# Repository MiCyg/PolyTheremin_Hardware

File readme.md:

# Polytheremin Hardware

[← Back to main repository](https://github.com/MiCyg/PolyTheremin.git)

---

# PolyTheremin Test Platform  

# Description  

This test platform features a main board with four capacitive proximity sensors based on [OpenTheremin](https://github.com/GaudiLabs/OpenThereminV4) electronics.  

The key improvement in this version is the replacement of the fixed-frequency oscillator with a microcontroller-driven heterodyne frequency generator. This modification simplifies the circuit design and calibration process.  

The platform enables the analysis of antenna correlation errors, visualized on an XY plot.  
Its ultimate goal is to provide a functional example of a PolyTheremin with four independent oscillators, significantly reducing finger cross-correlation.

# PCB Characteristics  
- **Microcontroller**: RP2040  
- **LED**: One addressable LED for status indication  
- **Oscillator Modules**: Four theremin modules, independently connected to the microcontroller  
- **Audio Output**: Four 12-bit DACs (MCP4922) with a mixer and a 6.3mm jack socket  

# Block Schematic  

# 3D View  

# Contribution  

Contributions are welcome!  
If you have suggestions, encounter any issues, or want to discuss the project, feel free to contact me or open a pull request.

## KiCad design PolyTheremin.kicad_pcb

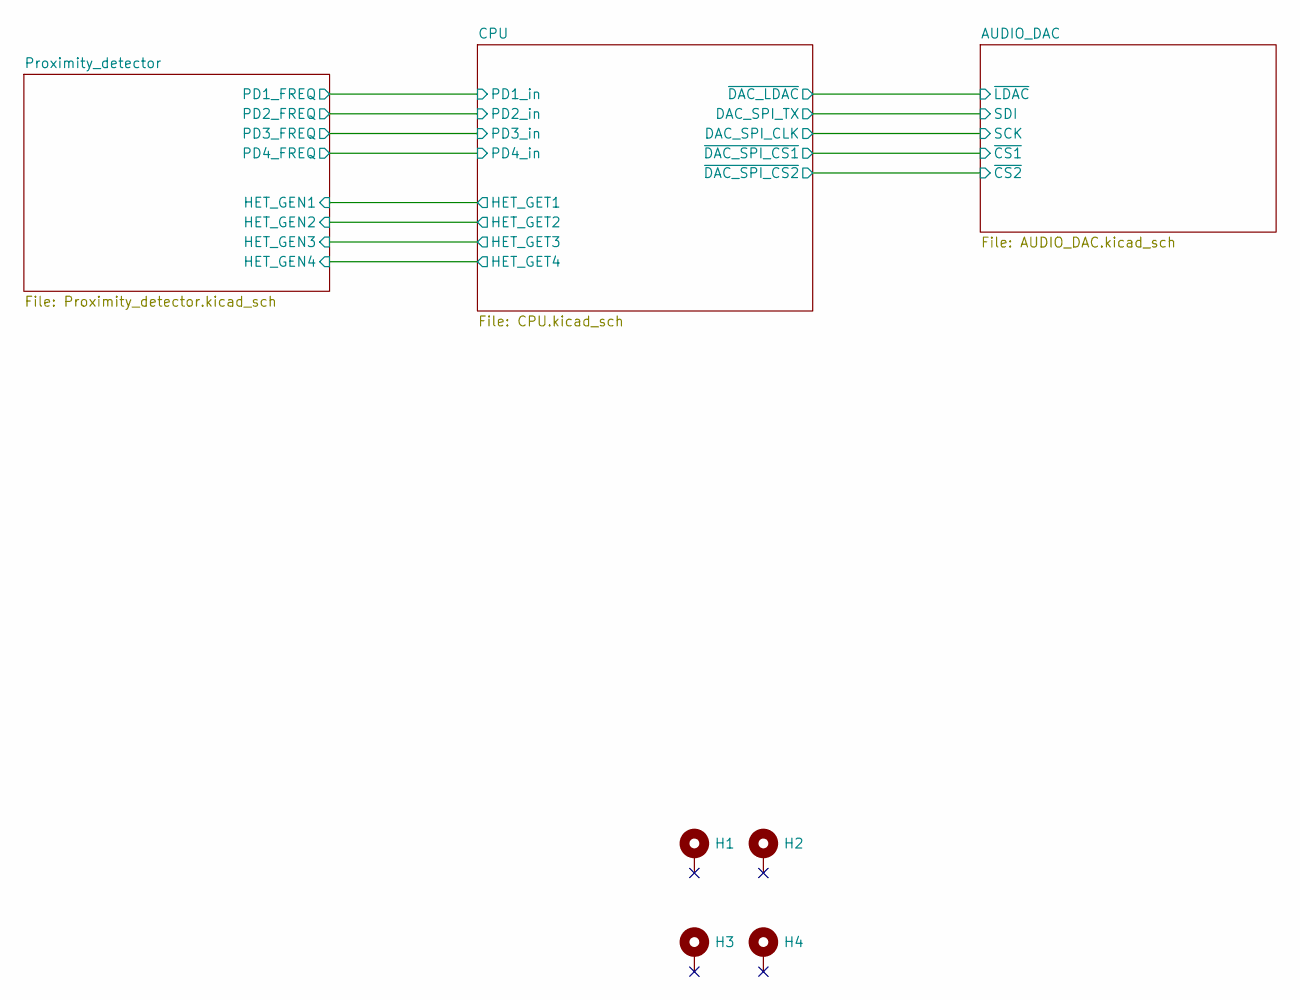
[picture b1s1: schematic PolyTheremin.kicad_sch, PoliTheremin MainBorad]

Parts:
H1, H2, H3, H4: MountingHole_Pad; MountingHole_3.2mm_M3_Pad_Via

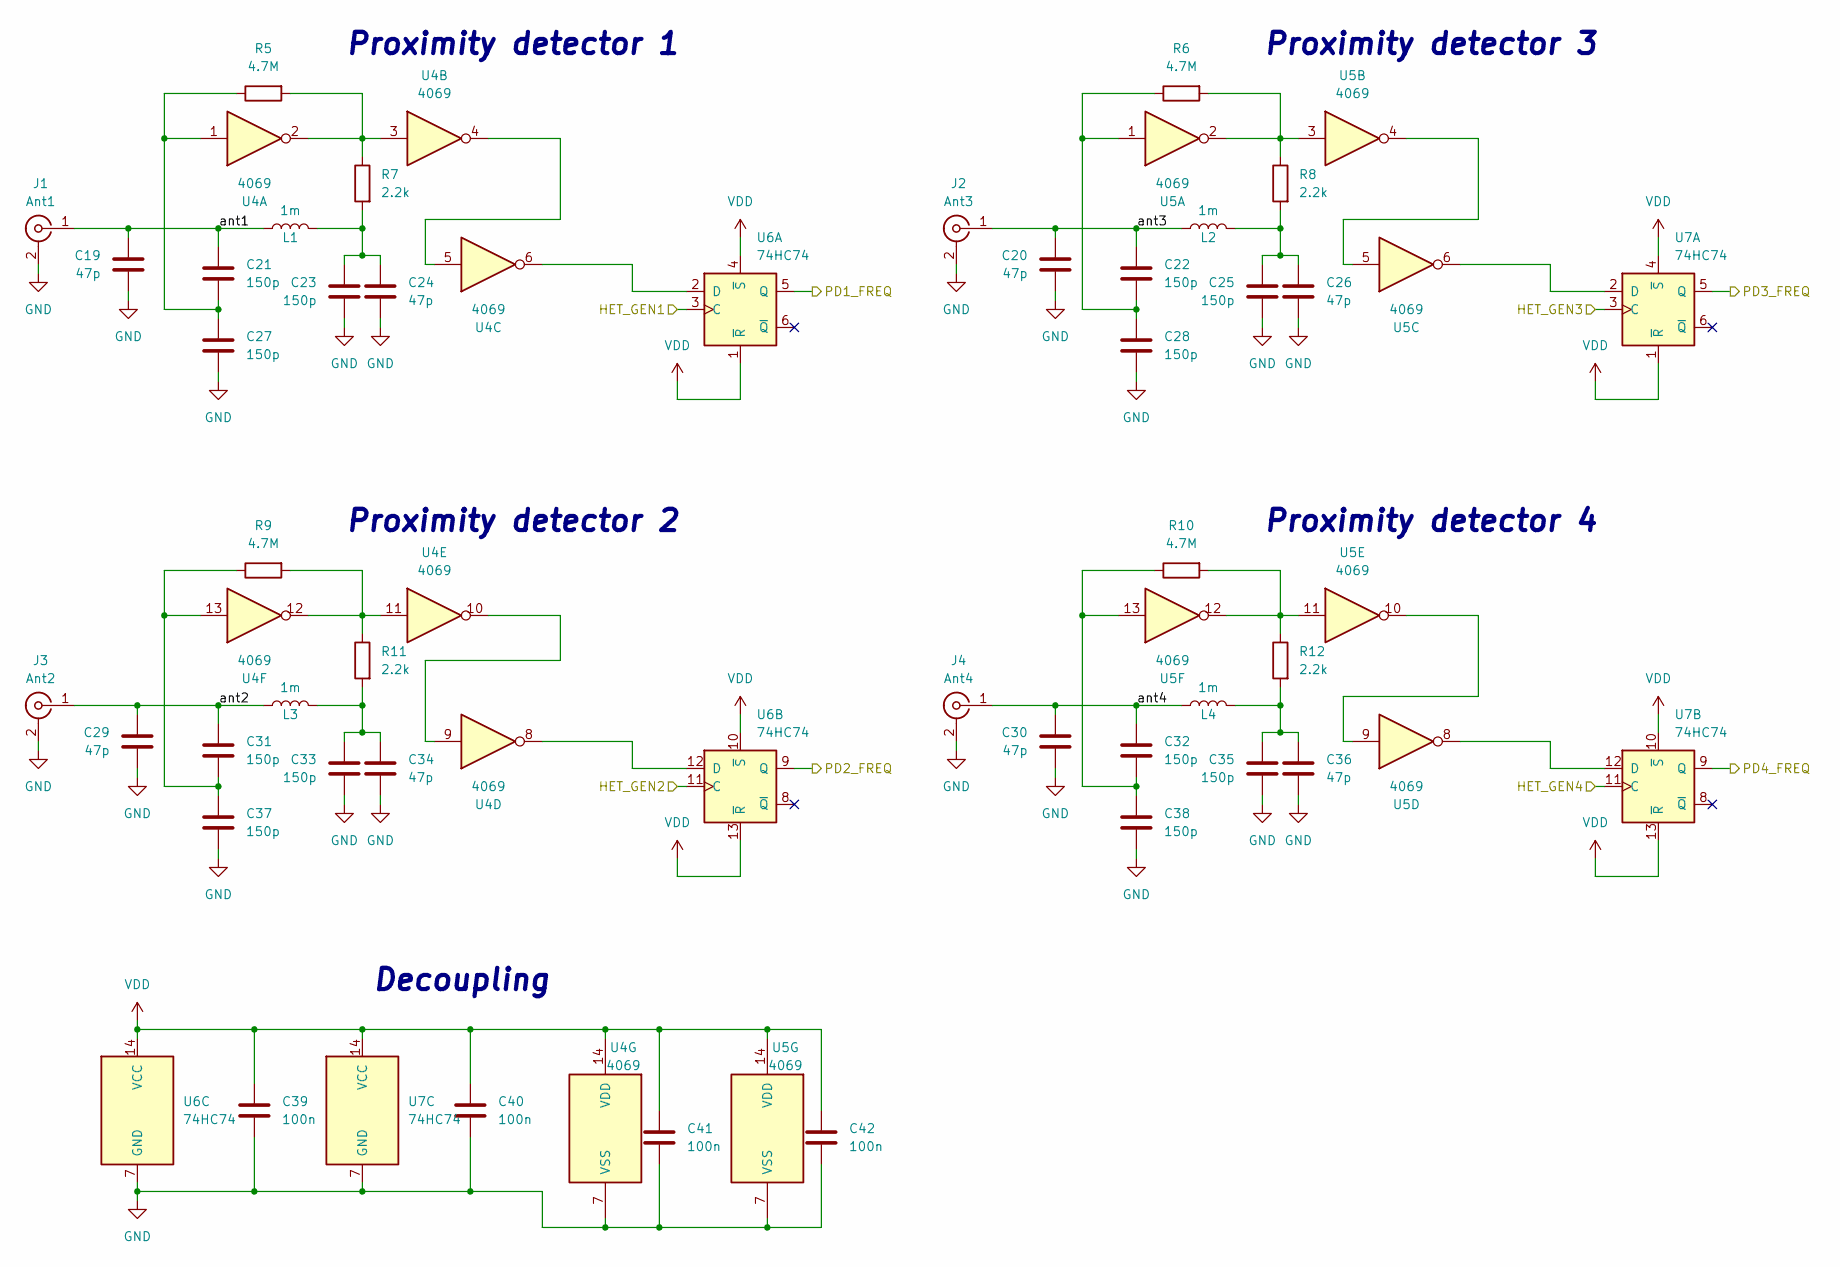
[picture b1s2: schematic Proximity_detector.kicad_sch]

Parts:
C19, C20, C24, C26, C29, C30, C34, C36: 47p; C_0603_1608Metric_Pad1.08x0.95mm_HandSolder
C21, C22, C23, C25, C27, C28, C31, C32, C33, C35, C37, C38: 150p; C_0603_1608Metric_Pad1.08x0.95mm_HandSolder
C39, C40, C41, C42: 100n; C_0603_1608Metric_Pad1.08x0.95mm_HandSolder
J1: Ant1; U.FL_Molex_MCRF_73412-0110_Vertical
J2: Ant3; U.FL_Molex_MCRF_73412-0110_Vertical
J3: Ant2; U.FL_Molex_MCRF_73412-0110_Vertical
J4: Ant4; U.FL_Molex_MCRF_73412-0110_Vertical
L1, L2, L3, L4: 1m; L_1812_4532Metric_Pad1.30x3.40mm_HandSolder
R5, R6, R9, R10: 4.7M; R_0603_1608Metric_Pad0.98x0.95mm_HandSolder
R7, R8, R11, R12: 2.2k; R_0603_1608Metric_Pad0.98x0.95mm_HandSolder
U4, U5: 4069; SOIC-14_3.9x8.7mm_P1.27mm
U6, U7: 74HC74; SOIC-14_3.9x8.7mm_P1.27mm

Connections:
/CPU/HET_GET1: U6.3 (C); also elsewhere on the board
/CPU/HET_GET2: U6.11 (C); also elsewhere on the board
/CPU/HET_GET3: U7.3 (C); also elsewhere on the board
/CPU/HET_GET4: U7.11 (C); also elsewhere on the board
/CPU/PD1_in: U6.5 (Q); also elsewhere on the board
/CPU/PD2_in: U6.9 (Q); also elsewhere on the board
/CPU/PD3_in: U7.5 (Q); also elsewhere on the board
/CPU/PD4_in: U7.9 (Q); also elsewhere on the board
/Proximity_detector/ant1: C19.1, C21.1, J1.1 (In), L1.2
/Proximity_detector/ant2: C29.1, C31.1, J3.1 (In), L3.2
/Proximity_detector/ant3: C20.1, C22.1, J2.1 (In), L2.2
/Proximity_detector/ant4: C30.1, C32.1, J4.1 (In), L4.2
GND: C19.2, C20.2, C23.2, C24.2, C25.2, C26.2, C27.2, C28.2, C29.2, C30.2, C33.2, C34.2, C35.2, C36.2, C37.2, C38.2, C39.2, C40.2, C41.2, C42.2, J1.2 (Ext), J2.2 (Ext), J3.2 (Ext), J4.2 (Ext), U4.7 (VSS), U5.7 (VSS), U6.7 (GND), U7.7 (GND); also elsewhere on the board
unnamed: C21.2, C27.1, R5.1, U4.1
unnamed: C22.2, C28.1, R6.1, U5.1
unnamed: C23.1, C24.1, L1.1, R7.2
unnamed: C25.1, C26.1, L2.1, R8.2
unnamed: C31.2, C37.1, R9.1, U4.13
unnamed: C32.2, C38.1, R10.1, U5.13
unnamed: C33.1, C34.1, L3.1, R11.2
unnamed: C35.1, C36.1, L4.1, R12.2
unnamed: R5.2, R7.1, U4.2, U4.3
unnamed: R6.2, R8.1, U5.2, U5.3
unnamed: R10.2, R12.1, U5.11, U5.12
unnamed: R9.2, R11.1, U4.11, U4.12
unnamed: U4.4, U4.5
unnamed: U4.9, U4.10
unnamed: U5.4, U5.5
unnamed: U5.9, U5.10
unnamed: U4.6, U6.2 (D)
unnamed: U4.8, U6.12 (D)
unnamed: U5.6, U7.2 (D)
unnamed: U5.8, U7.12 (D)
VDD: C39.1, C40.1, C41.1, C42.1, U4.14 (VDD), U5.14 (VDD), U6.1 (~R), U6.4 (~S), U6.10 (~S), U6.13 (~R), U6.14 (VCC), U7.1 (~R), U7.4 (~S), U7.10 (~S), U7.13 (~R), U7.14 (VCC); also elsewhere on the board

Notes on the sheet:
Decoupling
Proximity detector 1
Proximity detector 3
Proximity detector 4
Proximity detector 2

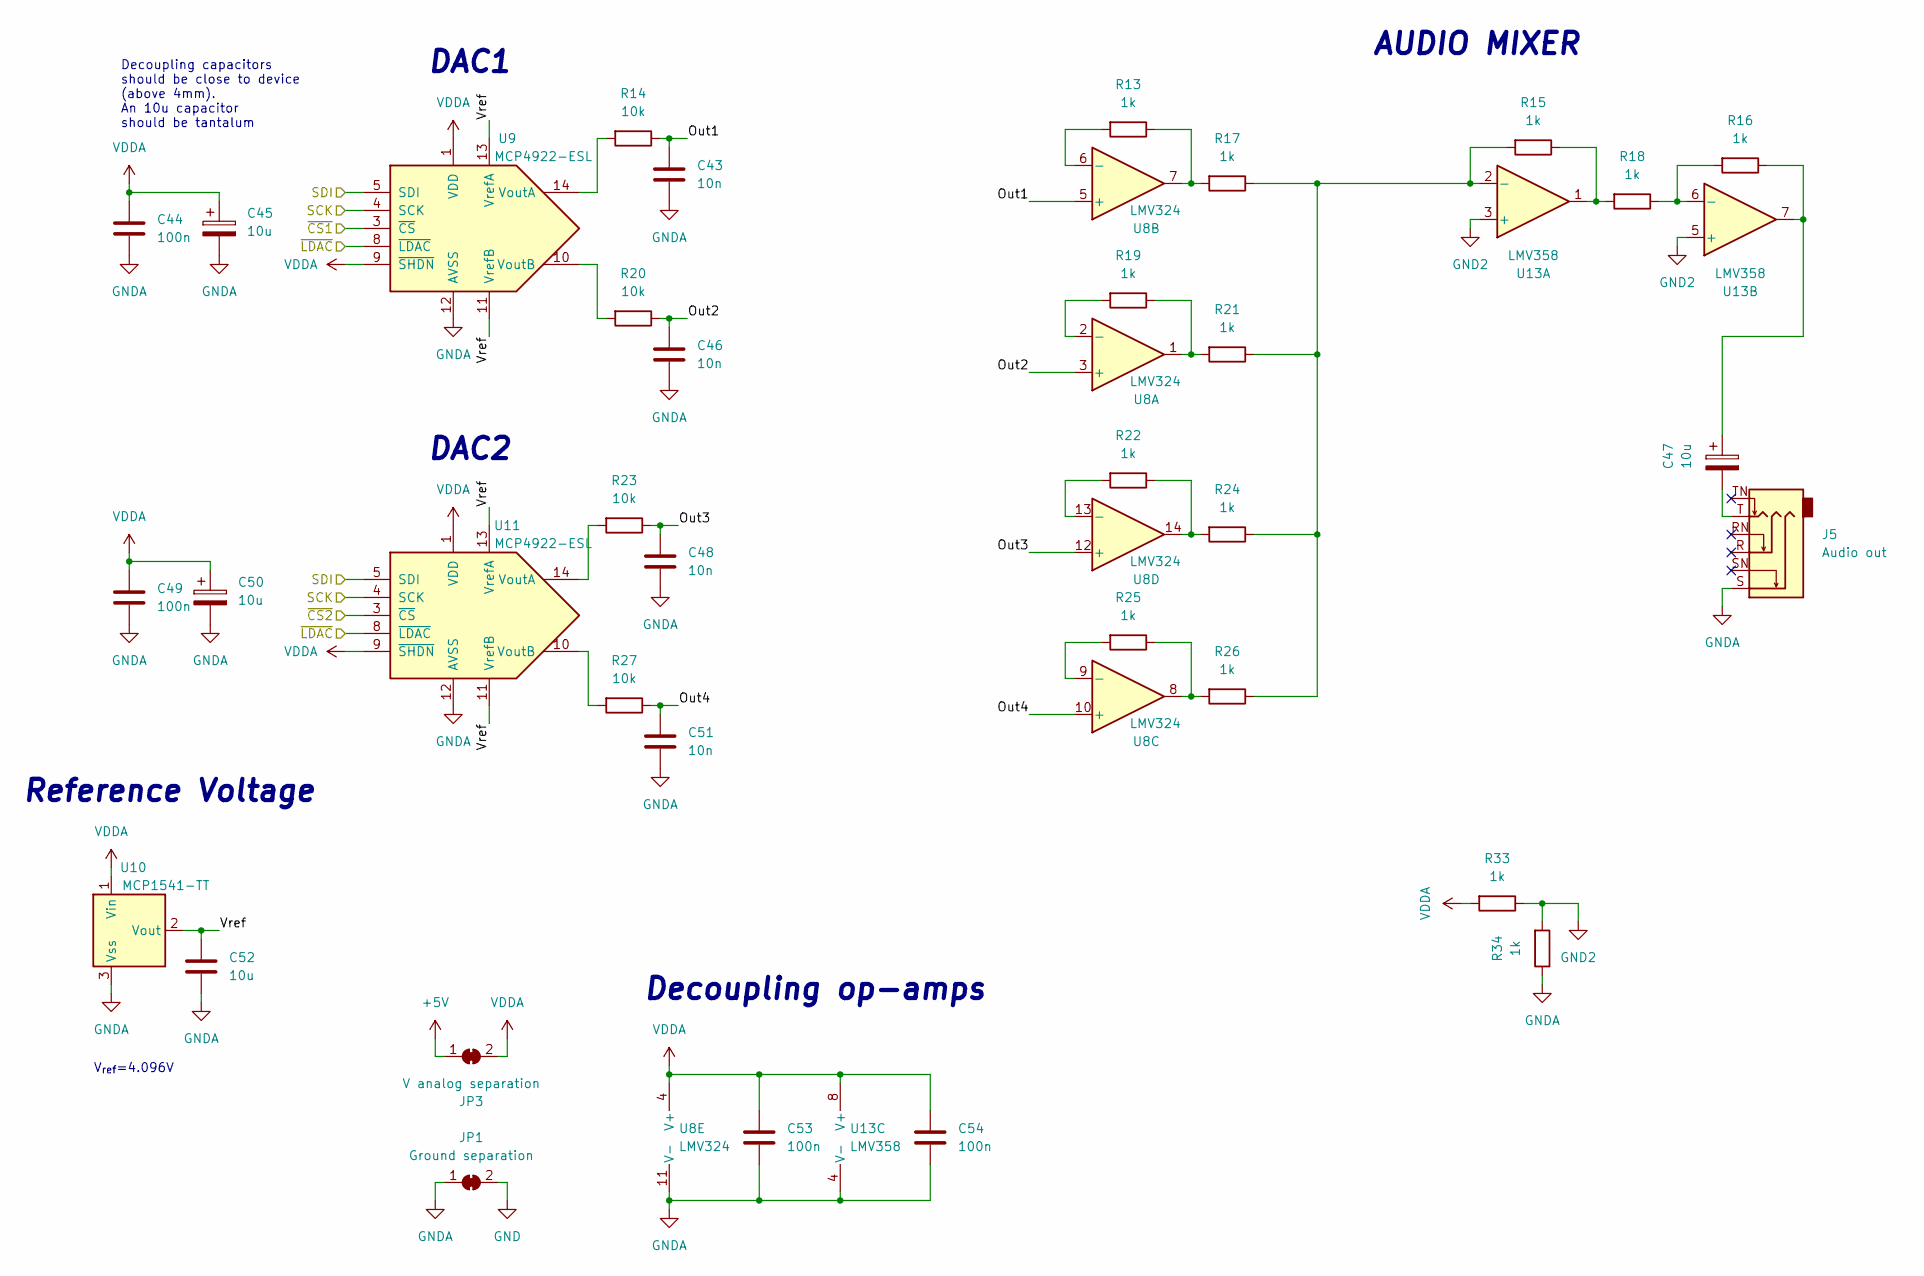
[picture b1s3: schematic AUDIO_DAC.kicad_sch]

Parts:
C43, C46, C48, C51: 10n; C_0603_1608Metric_Pad1.08x0.95mm_HandSolder
C44, C49, C53, C54: 100n; C_0603_1608Metric_Pad1.08x0.95mm_HandSolder
C45, C50: 10u; C_1206_3216Metric_Pad1.33x1.80mm_HandSolder
C47: 10u; C_0805_2012Metric_Pad1.18x1.45mm_HandSolder
C52: 10u; C_0603_1608Metric_Pad1.08x0.95mm_HandSolder
J5: Audio out; Jack_6.35mm_Neutrik_NMJ6HFD2_Horizontal
JP1: Ground separation; SolderJumper-2_P1.3mm_Open_RoundedPad1.0x1.5mm
JP3: V analog separation; SolderJumper-2_P1.3mm_Open_RoundedPad1.0x1.5mm
R13, R15, R16, R17, R18, R19, R21, R22, R24, R25, R26, R33, R34: 1k; R_0603_1608Metric_Pad0.98x0.95mm_HandSolder
R14, R20, R23, R27: 10k; R_0603_1608Metric_Pad0.98x0.95mm_HandSolder
U8: LMV324; SOIC-14_3.9x8.7mm_P1.27mm
U9, U11: MCP4922-ESL; SOIC-14_3.9x8.7mm_P1.27mm
U10: MCP1541-TT; SOT-23
U13: LMV358; SO-8_3.9x4.9mm_P1.27mm

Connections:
+5V: JP3.1 (A); also elsewhere on the board
/AUDIO_DAC/Out1: C43.1, R14.1, U8.5 (+)
/AUDIO_DAC/Out2: C46.1, R20.1, U8.3 (+)
/AUDIO_DAC/Out3: C48.1, R23.1, U8.12 (+)
/AUDIO_DAC/Out4: C51.1, R27.1, U8.10 (+)
/AUDIO_DAC/SCK: U9.4 (SCK), U11.4 (SCK); also elsewhere on the board
/AUDIO_DAC/SDI: U9.5 (SDI), U11.5 (SDI); also elsewhere on the board
/AUDIO_DAC/Vref: C52.1, U9.11 (VrefB), U9.13 (VrefA), U10.2 (Vout), U11.11 (VrefB), U11.13 (VrefA)
/AUDIO_DAC/~CS1: U9.3 (~CS); also elsewhere on the board
/AUDIO_DAC/~CS2: U11.3 (~CS); also elsewhere on the board
/AUDIO_DAC/~LDAC: U9.8 (~LDAC), U11.8 (~LDAC); also elsewhere on the board
GND: JP1.2 (B); also elsewhere on the board
unnamed: C47.1, R16.1, U13.7
unnamed: C47.2, J5.T
unnamed: R13.1, R17.2, U8.7
unnamed: R15.1, R18.2, U13.1
unnamed: R19.1, R21.2, U8.1
unnamed: R22.1, R24.2, U8.14
unnamed: R25.1, R26.2, U8.8
unnamed: R19.2, U8.2 (-)
unnamed: R13.2, U8.6 (-)
unnamed: R25.2, U8.9 (-)
unnamed: R22.2, U8.13 (-)
unnamed: R14.2, U9.14 (VoutA)
unnamed: R20.2, U9.10 (VoutB)
unnamed: R23.2, U11.14 (VoutA)
unnamed: R27.2, U11.10 (VoutB)
unnamed: R15.2, R17.1, R21.1, R24.1, R26.1, U13.2 (-)
unnamed: R16.2, R18.1, U13.6 (-)
VDDA: C44.1, C45.1, C49.1, C50.1, C53.1, C54.1, JP3.2 (B), R33.2, U8.4 (V+), U9.1 (VDD), U9.9 (~SHDN), U10.1 (Vin), U11.1 (VDD), U11.9 (~SHDN), U13.8 (V+)

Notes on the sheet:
AUDIO MIXER
Reference Voltage
DAC2
Decoupling op-amps
Decoupling capacitors should be close to device (above 4mm). An 10u capacitor should be tantalum
V_{ref}=4.096V
DAC1

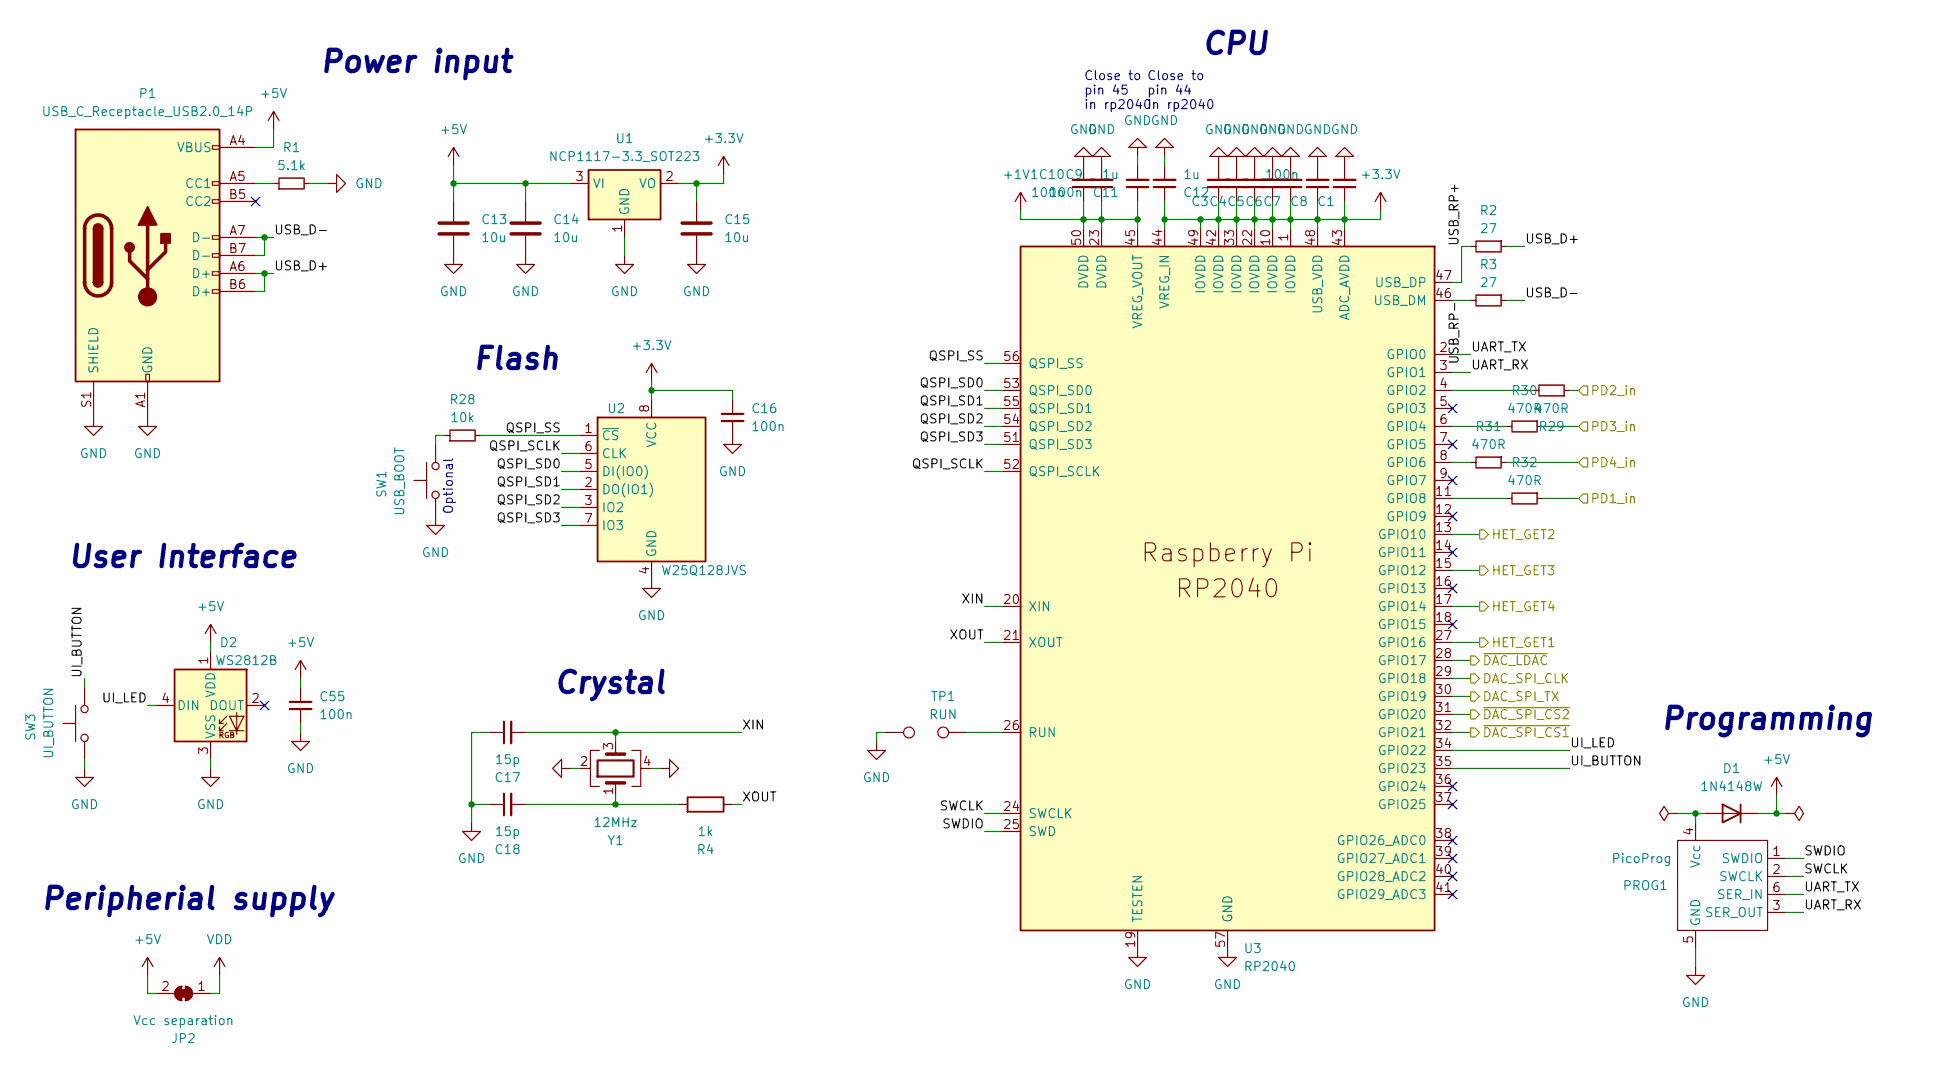
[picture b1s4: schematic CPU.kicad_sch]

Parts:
C1, C3, C4, C5, C6, C7, C8, C9, C10, C16, C55: 100n; C_0603_1608Metric_Pad1.08x0.95mm_HandSolder
C11, C12: 1u; C_0603_1608Metric_Pad1.08x0.95mm_HandSolder
C13, C14, C15: 10u; C_0805_2012Metric_Pad1.18x1.45mm_HandSolder
C17, C18: 15p; C_0603_1608Metric_Pad1.08x0.95mm_HandSolder
D1: 1N4148W; D_SOD-123
D2: WS2812B; LED_WS2812B_PLCC4_5.0x5.0mm_P3.2mm
JP2: Vcc separation; SolderJumper-2_P1.3mm_Open_RoundedPad1.0x1.5mm
P1: USB_C_Receptacle_USB2.0_14P; USB_C_Receptacle_G-Switch_GT-USB-7010ASV
PROG1: PicoProg; IDC-Header_2x03_P2.54mm_Vertical
R1: 5.1k; R_0603_1608Metric_Pad0.98x0.95mm_HandSolder
R2, R3: 27; R_0603_1608Metric_Pad0.98x0.95mm_HandSolder
R4: 1k; R_0603_1608Metric_Pad0.98x0.95mm_HandSolder
R28: 10k; R_0603_1608Metric_Pad0.98x0.95mm_HandSolder
R29, R30, R31, R32: 470R; R_0603_1608Metric_Pad0.98x0.95mm_HandSolder
SW1: USB_BOOT; SW_Tactile_SPST_Angled_PTS645Vx31-2LFS
SW3: UI_BUTTON; SW_Tactile_SPST_Angled_PTS645Vx31-2LFS
TP1: RUN
TP2: TestPoint
U1: NCP1117-3.3_SOT223; SOT-223-3_TabPin2
U2: W25Q128JVS; SOIC-8_5.23x5.23mm_P1.27mm
U3: RP2040; QFN-56-1EP_7x7mm_P0.4mm_EP3.2x3.2mm
Y1: 12MHz; Crystal_SMD_2520-4Pin_2.5x2.0mm

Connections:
+1V1: C9.1, C10.1, C11.1, U3.23 (DVDD), U3.45 (VREG_VOUT), U3.50 (DVDD)
+3.3V: C1.1, C3.1, C4.1, C5.1, C6.1, C7.1, C8.1, C12.1, C15.1, C16.1, U1.2 (VO), U2.8 (VCC), U3.1 (IOVDD), U3.10 (IOVDD), U3.22 (IOVDD), U3.33 (IOVDD), U3.42 (IOVDD), U3.43 (ADC_AVDD), U3.44 (VREG_IN), U3.48 (USB_VDD), U3.49 (IOVDD)
+5V: C13.1, C14.1, C55.1, D1.1 (K), D2.1 (VDD), JP2.2 (B), P1.A4 (VBUS), P1.A9 (VBUS), P1.B4 (VBUS), P1.B9 (VBUS), U1.3 (VI); also elsewhere on the board
/AUDIO_DAC/SCK: U3.29 (GPIO18); also elsewhere on the board
/AUDIO_DAC/SDI: U3.30 (GPIO19); also elsewhere on the board
/AUDIO_DAC/~CS1: U3.32 (GPIO21); also elsewhere on the board
/AUDIO_DAC/~CS2: U3.31 (GPIO20); also elsewhere on the board
/AUDIO_DAC/~LDAC: U3.28 (GPIO17); also elsewhere on the board
/CPU/HET_GET1: U3.27 (GPIO16); also elsewhere on the board
/CPU/HET_GET2: U3.13 (GPIO10); also elsewhere on the board
/CPU/HET_GET3: U3.15 (GPIO12); also elsewhere on the board
/CPU/HET_GET4: U3.17 (GPIO14); also elsewhere on the board
/CPU/PD1_in: R32.1; also elsewhere on the board
/CPU/PD2_in: R29.1; also elsewhere on the board
/CPU/PD3_in: R30.1; also elsewhere on the board
/CPU/PD4_in: R31.1; also elsewhere on the board
/CPU/QSPI_SCLK: U2.6 (CLK), U3.52 (QSPI_SCLK)
/CPU/QSPI_SD0: U2.5 (DI(IO0)), U3.53 (QSPI_SD0)
/CPU/QSPI_SD1: U2.2 (DO(IO1)), U3.55 (QSPI_SD1)
/CPU/QSPI_SD2: U2.3 (IO2), U3.54 (QSPI_SD2)
/CPU/QSPI_SD3: U2.7 (IO3), U3.51 (QSPI_SD3)
/CPU/QSPI_SS: R28.2, U2.1 (~CS), U3.56 (QSPI_SS)
/CPU/SWCLK: PROG1.2 (SWCLK), U3.24 (SWCLK)
/CPU/SWDIO: PROG1.1 (SWDIO), U3.25 (SWD)
/CPU/UART_RX: PROG1.3 (SER_OUT), U3.3 (GPIO1)
/CPU/UART_TX: PROG1.6 (SER_IN), U3.2 (GPIO0)
/CPU/UI_BUTTON: SW3.1, U3.35 (GPIO23)
/CPU/UI_LED: D2.4 (DIN), U3.34 (GPIO22)
/CPU/USB_D+: P1.A6 (D+), P1.B6 (D+), R2.1
/CPU/USB_D-: P1.A7 (D-), P1.B7 (D-), R3.1
/CPU/USB_RP+: R2.2, U3.47 (USB_DP)
/CPU/USB_RP-: R3.2, U3.46 (USB_DM)
/CPU/XIN: C17.2, U3.20 (XIN), Y1.3
/CPU/XOUT: R4.1, U3.21 (XOUT)
GND: C1.2, C3.2, C4.2, C5.2, C6.2, C7.2, C8.2, C9.2, C10.2, C11.2, C12.2, C13.2, C14.2, C15.2, C16.2, C17.1, C18.1, C55.2, D2.3 (VSS), P1.A1 (GND), P1.A12 (GND), P1.B1 (GND), P1.B12 (GND), P1.S1 (SHIELD), PROG1.5 (GND), R1.2, SW1.2, SW3.2, TP2.1, U1.1 (GND), U2.4 (GND), U3.19 (TESTEN), U3.57 (GND), Y1.2, Y1.4; also elsewhere on the board
unnamed: C18.2, R4.2, Y1.1
unnamed: D1.2 (A), PROG1.4 (Vcc)
unnamed: P1.A5 (CC1), R1.1
unnamed: R28.1, SW1.1
unnamed: TP1.1, U3.26 (RUN)
unnamed: R29.2, U3.4 (GPIO2)
unnamed: R30.2, U3.6 (GPIO4)
unnamed: R31.2, U3.8 (GPIO6)
unnamed: R32.2, U3.11 (GPIO8)
VDD: JP2.1 (A); also elsewhere on the board

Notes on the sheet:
Flash
Close to pin 44 in rp2040
Crystal
Close to pin 45 in rp2040
Peripherial supply
Optional
CPU
User Interface
Programming
Power input

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
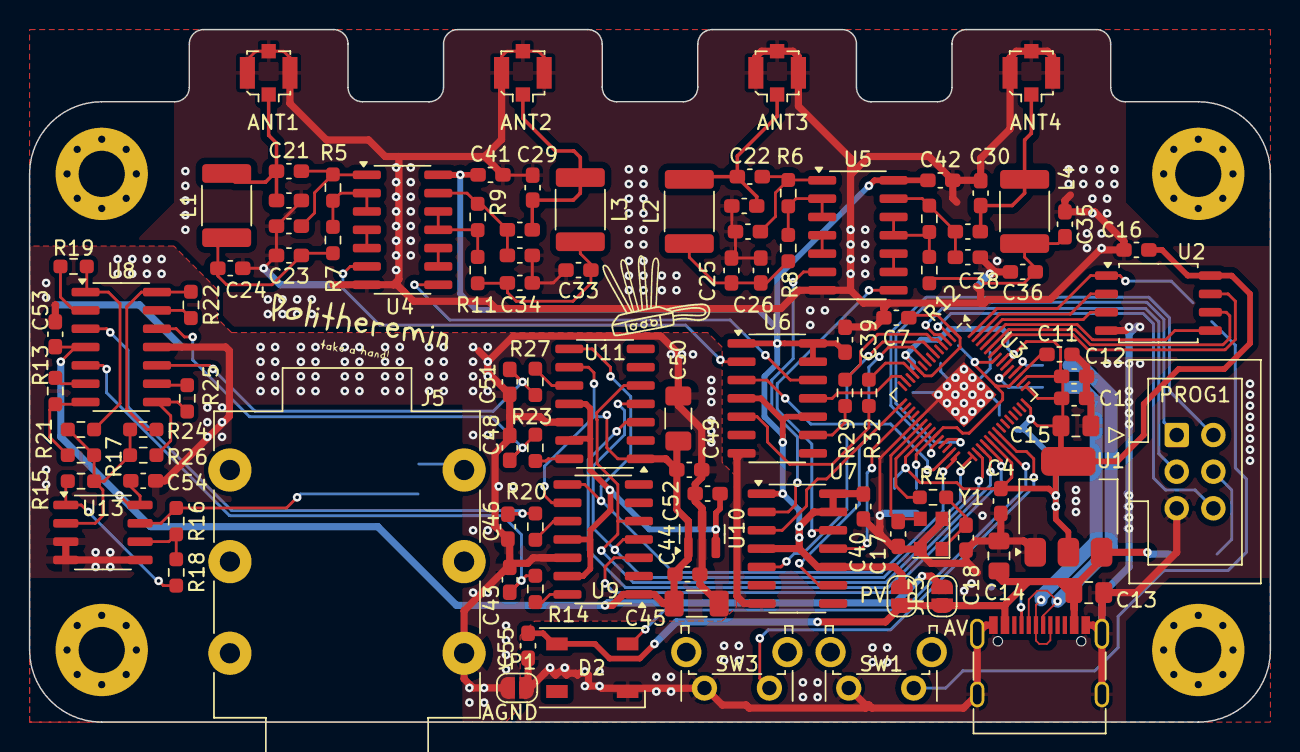
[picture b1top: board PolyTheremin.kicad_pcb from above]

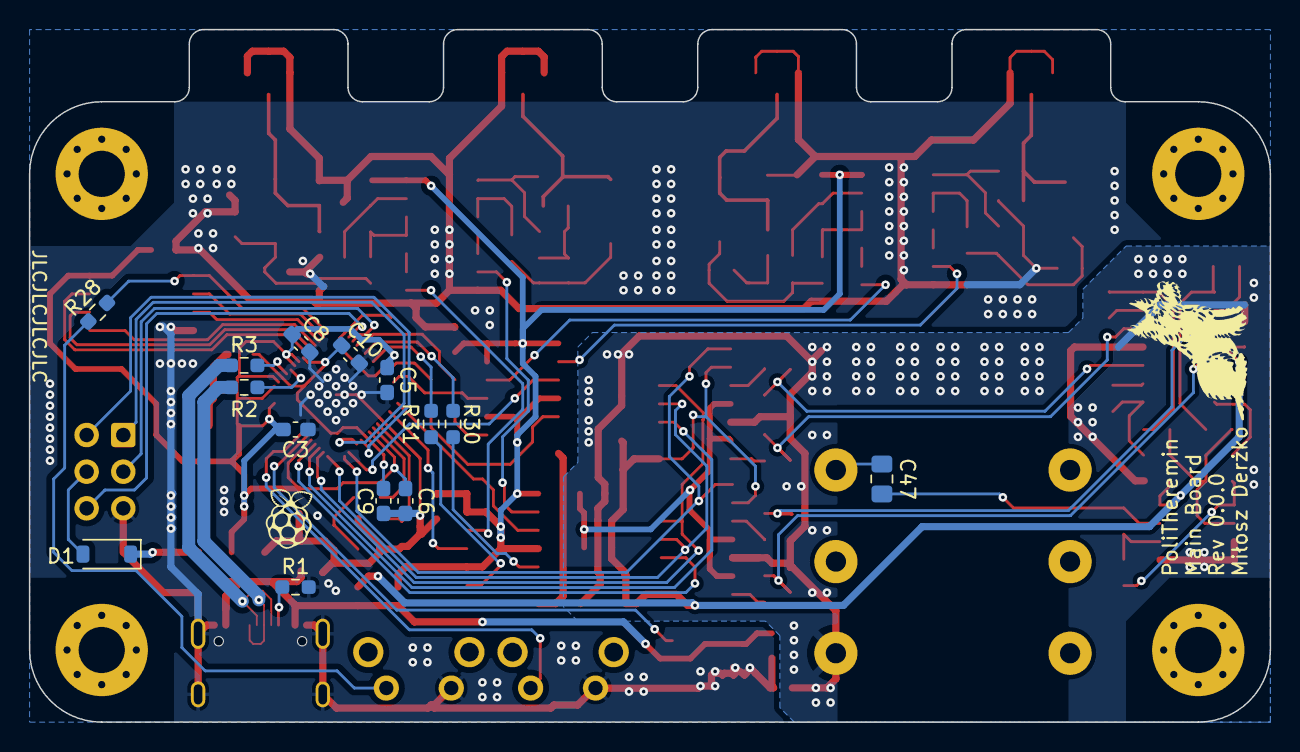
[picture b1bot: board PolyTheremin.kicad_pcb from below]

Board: 2 copper layers, 86.0 x 48.0 mm, 121 parts (14 on the bottom side), 92 nets.

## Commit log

2024-12-25 chore: git init
2024-12-25 chore: Add readme
2025-01-16 doc: Update readme
2025-01-18 feat: Add proper 3d footprint path
2025-01-18 feat: Update element path
2025-01-19 feat: Update path to eeprom
2025-01-19 feat: Update pdf schematic
2025-01-19 feat: Clean file structure
2025-10-03 fix: Remove second DAC
